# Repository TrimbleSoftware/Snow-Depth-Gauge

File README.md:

Snow-Depth-Gauge
================

Ultrasonic Wireless Snow Depth Gauge 

Source for Teensy 3.1 Firmware and Eagle 6.5.0 Schematic, 
PCB Layout and Parts list BOM for Trimble Ultrasonic Wireless Snow Depth Gauge.

Uses PRJC Teensy 3.1 microcontroller, MaxBotix ultrasonic sensor and
XBee Series 1 for wireless connectivity.

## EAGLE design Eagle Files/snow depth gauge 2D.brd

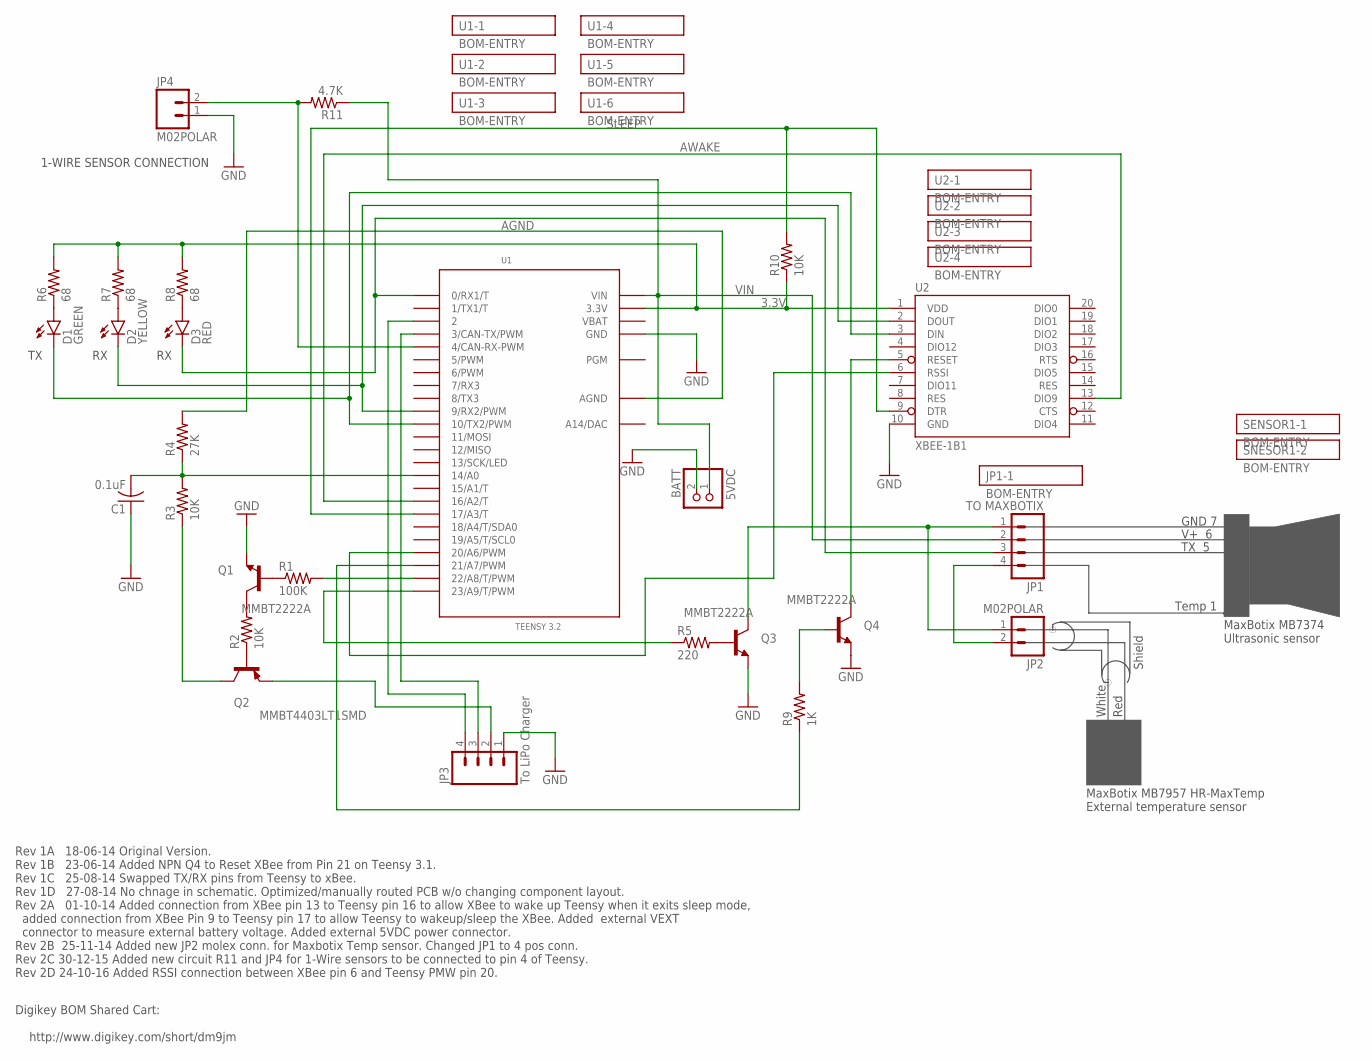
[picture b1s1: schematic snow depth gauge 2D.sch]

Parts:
BATT: 5VDC; JST-PH-2-SMT-RA; PARTNO S2B-PH-SM4-TB(LF)(SN)
C1: 0.1uF; C3216; PARTNO C1206C104K4RACTU
D1: GREEN; LED-0603; PARTNO LNJ337W83RA
D2: YELLOW; LED-0603; PARTNO LNJ437W84RA
D3: RED; LED-0603; PARTNO LNJ237W82RA
JP1: TO MAXBOTIX; MOLEX-1X4; PARTNO 0022292041
JP2, JP4: M02POLAR; MOLEX-1X2; PARTNO 0022292021
JP3: To LiPo Charger; MOLEX-1X4; PARTNO 0022292041
Q1, Q3, Q4: MMBT2222A; SOT23-BEC; PARTNO MMBT2222A
Q2: MMBT4403LT1SMD; SOT23-BEC; PARTNO MMBT4403
R1: 100K; R3216; PARTNO KTR18EZPJ104
R2, R3, R10: 10K; R3216; PARTNO KTR18EZPJ103
R4: 27K; R3216; PARTNO KTR18EZPJ273
R5: 220; R3216; PARTNO KTR18EZPJ221
R6, R7, R8: 68; R3216; PARTNO KTR18EZPF68R0
R9: 1K; R3216; PARTNO KTR18EZPJ102
R11: 4.7K; R3216; PARTNO KTR18EZPF4701
U1: TEENSY 3.2; TEENSY_3.1_BASIC; PARTNO TEENSY32
U2: XBEE-1B1; XBEE-1; PARTNO XB24-AUI-001

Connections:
3.3V: R6.2, R7.2, R8.2, R10.1, U1.3.3V, U1.3.3V1 (3.3V), U2.1 (VDD)
22: R1.2, U1.22/A8 (22/A8/T/PWM)
23: R5.1, U1.23/A9 (23/A9/T/PWM)
A0: C1.2, R3.2, R4.1, U1.14/A0
AGND: R4.2, U1.AGND
AWAKE: U1.16/A2 (16/A2/T), U2.13 (DIO9)
GND: BATT.2 (1), C1.1, JP3.1, JP4.1, Q1.E, Q3.E, Q4.E, U1.GND, U1.GND1 (GND), U2.10 (GND)
IN: D2.C, U1.9 (9/RX2/PWM), U2.2 (DOUT)
MBGND: JP1.1, JP2.1, Q3.C
MBTEMP: JP1.4, JP2.2
unnamed: D3.A, R8.1
unnamed: Q4.B, R9.2
unnamed: Q4.C, U2.5 (RESET)
unnamed: JP3.2, Q2.E
unnamed: Q3.B, R5.2
unnamed: Q1.B, R1.1
unnamed: Q1.C, R2.2
unnamed: Q2.B, R2.1
unnamed: D1.A, R6.1
unnamed: JP4.2, R11.2, U1.4 (4/CAN-RX-PWM)
unnamed: Q2.C, R3.1
unnamed: D2.A, R7.1
OUT: D1.C, U1.10 (10/TX2/PWM), U2.3 (DIN)
RESET: R9.1, U1.21/A7 (21/A7/PWM)
RSSI: U1.20/A6 (20/A6/PWM), U2.6 (RSSI)
RX1: D3.C, JP1.3, U1.0 (0/RX1/T)
SLEEP: R10.2, U1.17/A3 (17/A3/T), U2.9 (DTR)
STAT1: JP3.4, U1.2
STAT2: JP3.3, U1.3 (3/CAN-TX/PWM)
VBAT: U1.VBAT
VIN: BATT.1 (2), JP1.2, R11.1, U1.VIN

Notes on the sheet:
Rev 1A 18-06-14 Original Version. Rev 1B 23-06-14 Added NPN Q4 to Reset XBee from Pin 21 on Teensy 3.1. Rev 1C 25-08-14 Swapped TX/RX pins from Teensy to xBee. Rev 1D 27-08-14 No chnage in schematic. Optimized/manually routed PCB w/o changing component layout. Rev 2A 01-10-14 Added connection from 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
Digikey BOM Shared Cart: http://www.digikey.com/short/dm9jm
GND 7
V+ 6
TX 5
MaxBotix MB7374 Ultrasonic sensor
Temp 1
MaxBotix MB7957 HR-MaxTemp External temperature sensor
Red
White
Shield
1-WIRE SENSOR CONNECTION

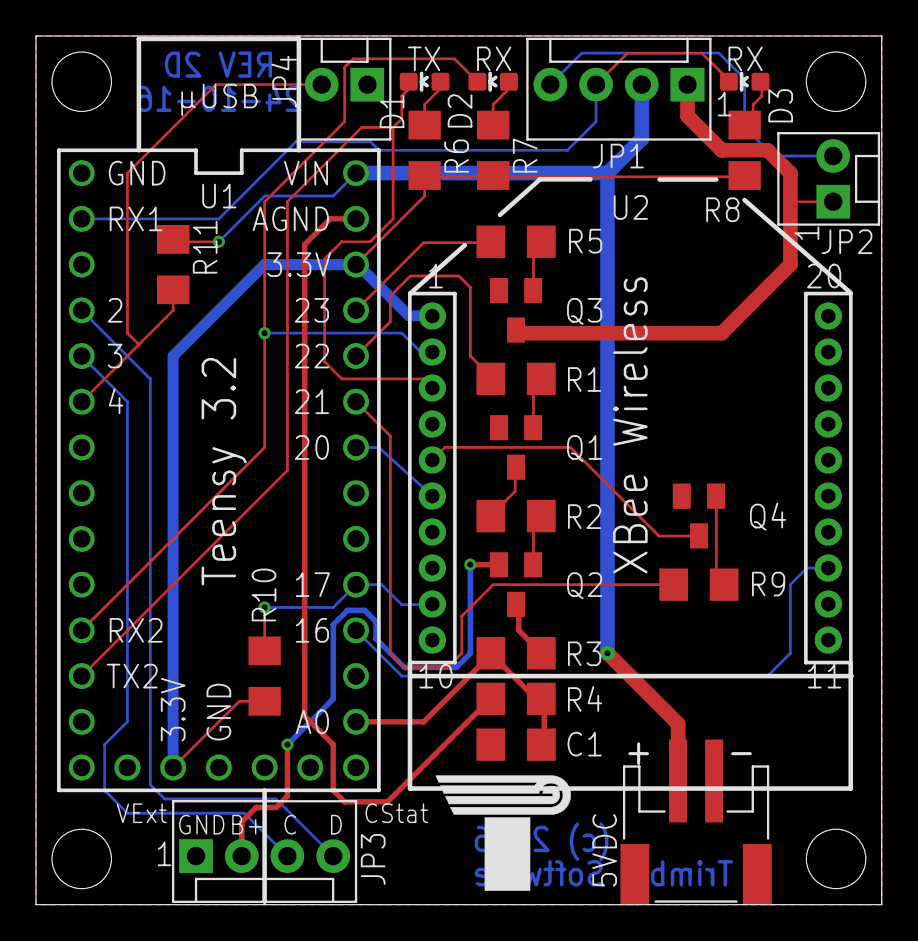
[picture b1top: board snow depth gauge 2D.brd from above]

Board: 2 copper layers, 47.0 x 48.3 mm, 32 parts (0 on the bottom side), 30 nets.

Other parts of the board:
U$1, U$2, U$3, U$4: STAND-OFF
U$5: LOGO_4
U$6: LOGO_4_BOTTOM

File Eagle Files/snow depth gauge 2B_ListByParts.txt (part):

Part      Value           Attributes Package          Description                                                                     Part Num              Mfg Name                        VID Vendor Part Num         Description                                                    Pkg Code XREF 
BATT      5VDC                       JST-PH-2-SMT-RA  JST 2-Pin Connectors of various flavors                                         S2B-PH-SM4-TB(LF)(SN) JST Sales America Inc           DK  455-1749-1-ND           CONN HEADER PH SIDE 2POS 2MM SMD                               *        REF33
C1        0.1uF                      C3216            CAPACITOR, American symbol                                                      C1206C104K4RACTU      Kemet                           DK  399-9305-1-ND           CAP CER 0.1UF 16V 10% X7R 1206                                 C3216    REF4 
D1        GREEN                      LED-0603         Various green LEDs                                                              LNJ337W83RA           Panasonic Electronic Components DK  LNJ337W83RACT-ND        LED GREEN HIGH BRIGHT ESS SMD                                  0603     REF1 
D2        YELLOW                     LED-0603         Yellow SMD LEDs                                                                 LNJ437W84RA           Panasonic Electronic Components DK  LNJ437W84RACT-ND        LED AMBER HIGH BRIGHT ESS SMD                                  0603     REF2 
D3        RED                        LED-0603         Assorted Red LEDs                                                               LNJ237W82RA           Panasonic Electronic Components DK  LNJ237W82RACT-ND        LED RED HIGH BRIGHT ESS SMD                                    0603     REF3 
JP1       TO MAXBOTIX                MOLEX-1X4        Header 4                                                                        0022292041            Molex Inc                       DK  WM2746-ND               CONN HEADER 4POS .100 VERT GOLD                                *        REF9 
JP1-1     BOM-ENTRY                  *                BOM ENTRY                                                                       PRT-09920             Sparkfun                        SF  MOLEX_TO_MOLEX_13_II_07 Molex Jumper 4 Wire Assembly 6" Long                           *        REF26
JP2       M02POLAR                   MOLEX-1X2        Standard 2-pin 0.1" header. Use with                                            0022292021            Molex Inc                       DK  WM2744-ND               CONN HEADER 2POS .100 VERT GOLD                                *        REF11
JP3       To LiPo Charger            MOLEX-1X4        Header 4                                                                        0022292041            Molex Inc                       DK  WM2746-ND               CONN HEADER 4POS .100 VERT GOLD                                *        REF9 
Q1        MMBT2222A                  SOT23-BEC        NPN Transistror                                                                 MMBT2222A             Fairchild Semiconductor         DK  MMBT2222AFSCT-ND        TRANSISTOR GP NPN AMP SOT-23                                   SOT23    REF7 
Q2        MMBT4403LT1SMD             SOT23-BEC        PNP Transistror                                                                 MMBT4403              Fairchild Semiconductor         DK  MMBT4403FSCT-ND         TRANSISTOR GP PNP AMP SOT-23                                   SOT23    REF8 
Q3        MMBT2222A                  SOT23-BEC        NPN Transistror                                                                 MMBT2222A             Fairchild Semiconductor         DK  MMBT2222AFSCT-ND        TRANSISTOR GP NPN AMP SOT-23                                   SOT23    REF7 
Q4        MMBT2222A                  SOT23-BEC        NPN Transistror                                                                 MMBT2222A             Fairchild Semiconductor         DK  MMBT2222AFSCT-ND        TRANSISTOR GP NPN AMP SOT-23                                   SOT23    REF7 
R1        100K                       R3216            RESISTOR, American symbol                                                       KTR18EZPJ104          Rohm Semiconductor              DK  RHM100KPCT-ND           RES 100K OHM 1/4W 5% 1206 SMD                                  R3216    REF17
R2        10K                        R3216            RESISTOR, American symbol                                                       KTR18EZPJ103          Rohm Semiconductor              DK  RHM10KPCT-ND            RES 10K OHM 1/4W 5% 1206 SMD                                   R3216    REF13
R3        10K                        R3216            RESISTOR, American symbol                                                       KTR18EZPF1002         Rohm Semiconductor              DK  RHM10.0KAICT-ND         RES SMD 10K OHM 1% 1/4W 1206                                   R3216    REF14
R4        27K                        R3216            RESISTOR, American symbol                                                       KTR18EZPF2702         Rohm Semiconductor              DK  RHM27KAICT-ND           RES SMD 27K OHM 1% 1/4W 1206                                   R3216    REF16
R5        220                        R3216            RESISTOR, American symbol                                                       KTR18EZPJ221          Rohm Semiconductor              DK  RHM220PCT-ND            RES 220 OHM 1/4W 5% 1206 SMD                                   R3216    REF19
R6        68                         R3216            RESISTOR, American symbol                                                       KTR18EZPJ680          Rohm Semiconductor              DK  RHM68PCT-ND             RES 68 OHM 1/4W 5% 1206 SMD                                    R3216    REF12
R7        68                         R3216            RESISTOR, American symbol                                                       KTR18EZPJ680          Rohm Semiconductor              DK  RHM68PCT-ND             RES 68 OHM 1/4W 5% 1206 SMD                                    R3216    REF12
R8        68                         R3216            RESISTOR, American symbol                                                       KTR18EZPJ680          Rohm Semiconductor              DK  RHM68PCT-ND             RES 68 OHM 1/4W 5% 1206 SMD                                    R3216    REF12
R9        1K                         R3216            RESISTOR, American symbol                                                       KTR18EZPJ102          Rohm Semiconductor              DK  RHM1.0KPCT-ND           RES 1K OHM 1/4W 5% 1206 SMD                                    R3216    REF18
R10       10K                        R3216            RESISTOR, American symbol                                                       KTR18EZPJ103          Rohm Semiconductor              DK  RHM10KPCT-ND            RES 10K OHM 1/4W 5% 1206 SMD                                   R3216    REF13
SENSOR1-1 BOM-ENTRY                  *                BOM ENTRY                                                                       MB7374                MaxBotix Inc.                   MB  MB7374                  HRXL-MaxSonar - WRS Series Ultrasonic Snow Depth Sensor MB7374 *        REF31
SNESOR1-2 BOM-ENTRY                  *                BOM ENTRY                                                                       MB7957                MaxBotix Inc.                   MB  MB7957                  HR-MaxTemp MB7957                                              *        REF30
U1        TEENSY 3.1                 TEENSY_3.1_BASIC Footprint for Teensy 3.1 board using all pin connections on the outer perimeter TEENSY31              PRJC.COM                        PR  TEENSY31                Teensy USB Board, Version 3.1                                  *        REF32
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
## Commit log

2014-09-18 Teensy 3.1 sketch source
    Version 1.3 of Teensy/Maxbotix Snow Depth Gauge
2014-09-18 Eagle Files
    Eagle files for PCB fabrication.
2014-09-18 Revert "Eagle Files"
    This reverts commit d98600f46fc9b085ccf87501f4de8b5395eab803.
2014-09-18 Teensy 3.1 Firmware
    Teensy 3.1 sketch for Snow Depth Gauge Firmware
2014-09-18 Eagle Files
    Eagle Files for PCB Fabrication and BOM
2014-09-18 updated readme file
2014-09-18 Meteohub Plugin
    gcc source for meteohub plug-in for Trimble Ultrasonic Wireless Snow
    Depth Gauge
2014-09-22 updated for file pull
2014-09-22 Version 1.0
    version updated and one bug fix
2014-10-02 Remote reset fixes
    Fixed problem with remote sensor reset on plugin startup
2014-10-02 Improved PCB version 2A. Not tested yet.
    Designed to interface to Adafriut Solar LiPo Charger for Status Charging
    and Done, connection to XBee sleep pin and measurement of voltage from
    external source (ala external LiPo battery).
2014-10-24 Added outlier removal and data smoothing
    Added outlier removal and data smoothing. any value that is more than 3
    standard deviations away from the mean of the last 10 readings is
    replaced by the average of the last 10 readings. Data is now smoothed
    using a moving average (aka rolling average) of the last 10 readings.
    Also added a test program to demonstrate the smoothing and a utility to
    dump the binary array stored in a file of the last 10 readings.
2014-11-10 Ver. 1.2
    Added Standard Deviation filter limit value to .config file. Also
    re-read array from disc at end of polling loop to allow changes to be
    made to the moving average values with out restarting the program.
2014-11-26 PCB Ver. 2B
    Further Improved PCB Version 2B. Not tested yet. Has 4 pin and Molex
    conn. for Maxbotix snow sensor and 2 pin Molex conn. for Maxbotix Temp
    sensor and 4 pin Molex for LiPo charger connections.
2014-11-27 Ver 1.3
    Ver 1.3 Changed to read sma array values from sensor at startup instead
    from saved file. Added logic to get_depth_value
    and get_range_value to allow better reporting on specific sensor errors.
2014-11-28 Ver 1.4
    Fix spelling typo
2014-12-01 Ver 1.3a
    cleaned up some startup problems introduced in Ver 1.3.
2014-12-01 Ver 1.3a
    Fixed some typos.
2014-12-02 Ver 1.3a
    Added additional condition during sma array initialization
2014-12-03 Ver 1.4
    Added retry logic to depth, range and auto calibrate functions
2014-12-05 Ver 1.5
    Added retry count to .conf file
2015-01-10 Makefile for raspbian
    Makefile edited for rpi raspbian uname
2015-01-13 PCB Ver. 2B Voltage Divider Update
    Updated voltage divider components and values for measuring external 4.2
    VDC LiPo battery.
2015-03-07 Ver 1.6
    Ver 1.6 Added reread of sma array when stddev is out of range
2015-05-07 Makefile for raspbian on PI 2
    Changes to Makefile for raspbian running on Raspberry PI 2 B host.
2015-05-07 Cleanup Makefile for rpi & rpi2
    Edit and cleanup Makefile to work better on Debian and Raspbian meteohub
    kernels.
2015-09-06 Ver 1.5
    Code changes for hardware ver 2B integration with Adafriut solar charger
    http://www.adafruit.com/products/390
    and xBee hardware wake/sleep on pin 17.
    http://www.fiz-ix.com/2012/11/low-power-xbee-sleep-mode-with-arduino-and-pin-hibernation/
2015-09-07 Ver 1.7
    Ver 1.7 Added LiPo charger status output for Snow Depth Gauge Version
    2B-1.5
2016-07-08 Xbee radio config updates
    Added firmware version to file name and added Xbee Pro config profiles.
2016-07-08 Updates for Arduino 1.6.6
    Updated to compile with Arduino 1.6.6 by commenting out #ifdefs for
    _cextern "C" on startup_early_hook() function.
2016-09-14 Bumped minor version mumber
    Bumped minor version for Arduino 1.6.6 compiled binary
2016-09-14 Added date to ver number
2016-09-23 Changes for Arduino 1.6.11 and Teensyduino 1.30
    Code changes to build with Arduino 1.6.11 and Teensyduino 1.30 and
    LowPower_Teensy3 library.
2016-11-21 Revert back to Arduino 1.0.6 and Teensyduino 1.20
    Revert code back to compile with Arduino 1.0.6 and Teensyduino 1.20 to
    try and get wathdog timer working properly.
2016-11-23 Added new command I
    Version 1.6d 22-Nov-2016 Added new command I to display firmware build
    info
2016-12-06 minor bug fix on about logging
2017-01-06 Added code to clear incomming serial data after current command has completed.
    Version 1.6e 05-Jan-2017 Added code to clear incomming serial data
    after current command has completed in at attempt to discard bad data
    that sometime hangs the teensy.
2017-01-06 Version 1.6e 05-Jan-2017
    Version 1.6e 05-Jan-2017 Added code to clear incomming serial data
    after current command has completed in at attempt to discard bad data
    that sometime hangs the teensy.
2017-01-10 Ver 1.7a
    Ver 1.7a Added code to set tty file to non buffered and added mandentory
    delay when
2017-01-12 Ver 1.7a minor bug fixes
    minor bug fixes for readings file as read from config
2017-01-12 Ver 1.7a more minor bug fixes
    minor bug fixes for sensor readings file config and writing.
2017-01-25 Ver 2.0
    Ver 2.0 changed i/o to fd non-buffered using poll() and looping to
    read/write tty data and added retry logic to sensor reading functions.
2017-01-25 Revert "Ver 2.0"
    This reverts commit 12273f9cdc06bfb025c33b7855a577ee9c001226.
2017-01-25 Ver 2.0
    Ver 2.0 changed i/o to fd non-buffered using poll() and looping to
    read/write tty data and added retry logic to some sensor reading
    functions.
2017-01-25 Ver 2.0
    Minor change. Refined saving existing termios settings
2017-02-01 Ver 2.0a
    Ver 2.0a added main loop exit via return codes propigated through sensor
    readings. To allow meteohub to restart plugin when comm errors occure.
2017-03-13 Ver 2.0b
    Ver 2.0b bug fixes in avarage amd moving average functions and initial
    sensor readings functions.
2017-03-21 Version 1.7a
    Version 1.7a 20-Mar-2017 Added new command N to read XBee RSSI from pin
    6 using PWM and display as relative signal strength percentage.
2017-04-05 Eagle files for PCB Ver 2D 24-10-16
    Added RSSI conection between XBee pin 6 and Teensy PWN pin 20
2017-04-05 New .hex file for ver 1.7a

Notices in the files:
Eagle Files/snow depth gauge 2D.brd:
(c) 2016
parts and their libraries:
SparkFun-Electromechanical: Licensing: Creative Commons ShareAlike 4.0 International - https://creativecommons.org/licenses/by-sa/4.0
bom: Copyright (C) 2010, Bob Starr
